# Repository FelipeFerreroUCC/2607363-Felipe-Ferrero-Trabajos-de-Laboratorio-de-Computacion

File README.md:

# 2607363-Felipe-Ferrero-Microduino

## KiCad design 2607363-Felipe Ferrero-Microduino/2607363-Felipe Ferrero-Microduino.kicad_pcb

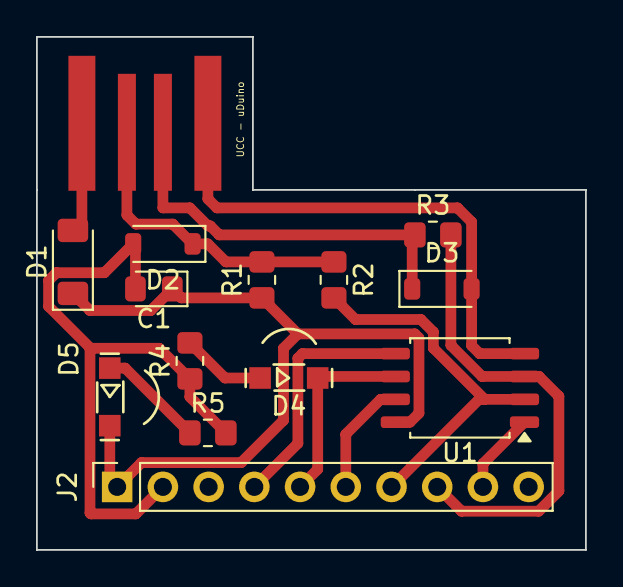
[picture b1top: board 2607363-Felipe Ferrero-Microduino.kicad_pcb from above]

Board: 2 copper layers, 30.5 x 28.5 mm, 14 parts (0 on the bottom side), 13 nets.

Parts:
C1: 0.1u; D_0805_2012Metric_Pad1.15x1.40mm_HandSolder
D1: PMLL4148L; D_MiniMELF
D2, D3: 3.6V 1/2mW; D_SOD-123
D4: LED Green; LED.R
D5: LED Red; LED.R
J1: USB_A; USB_A_UCC
J2: Header; PinSocket_1x10_P2.54mm_Vertical
R1: 1.5KΩ 5% 1/8W; R_0805_2012Metric_Pad1.20x1.40mm_HandSolder
R2, R3: 330Ω 5% 1/8W; R_0805_2012Metric_Pad1.20x1.40mm_HandSolder
R4, R5: 68Ω 5% 1/8W; R_0805_2012Metric_Pad1.20x1.40mm_HandSolder
U1: ATtiny85-20S; SOIC-8_5.3x5.3mm_P1.27mm

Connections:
+5V: C1.1, D1.1 (K), D5.2 (A), J2.1, R1.1, U1.8 (VCC)
GND: C1.2, D2.2 (A), D3.2 (A), J1.4 (GND), J2.2, R4.1, R5.2, U1.4 (GND)
unnamed: D1.2 (A), J1.1 (VBUS)
unnamed: D2.1 (K), J1.2 (D-), R1.2, R2.1
unnamed: D3.1 (K), J1.3 (D+), R3.1
unnamed: D4.2 (A), J2.5, U1.6 (PB1)
unnamed: D4.1 (K), R4.2
unnamed: D5.1 (K), R5.1
unnamed: J2.4, U1.5 (AREF/PB0)
unnamed: J2.6, U1.7 (PB2)
unnamed: J2.7, R2.2, U1.2 (XTAL1/PB3)
unnamed: J2.8, R3.2, U1.3 (XTAL2/PB4)
unnamed: J2.9, U1.1 (~RESET/PB5)

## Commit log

2026-05-27 2607363-Felipe Ferrero-Microduino
2026-05-29 Mi prrimer commit y entrga de protecto de kicad
2026-05-29 Actualización Microduino
2026-05-29 Ignorar carpeta .history
2026-06-03 Agrego nueva carpeta
